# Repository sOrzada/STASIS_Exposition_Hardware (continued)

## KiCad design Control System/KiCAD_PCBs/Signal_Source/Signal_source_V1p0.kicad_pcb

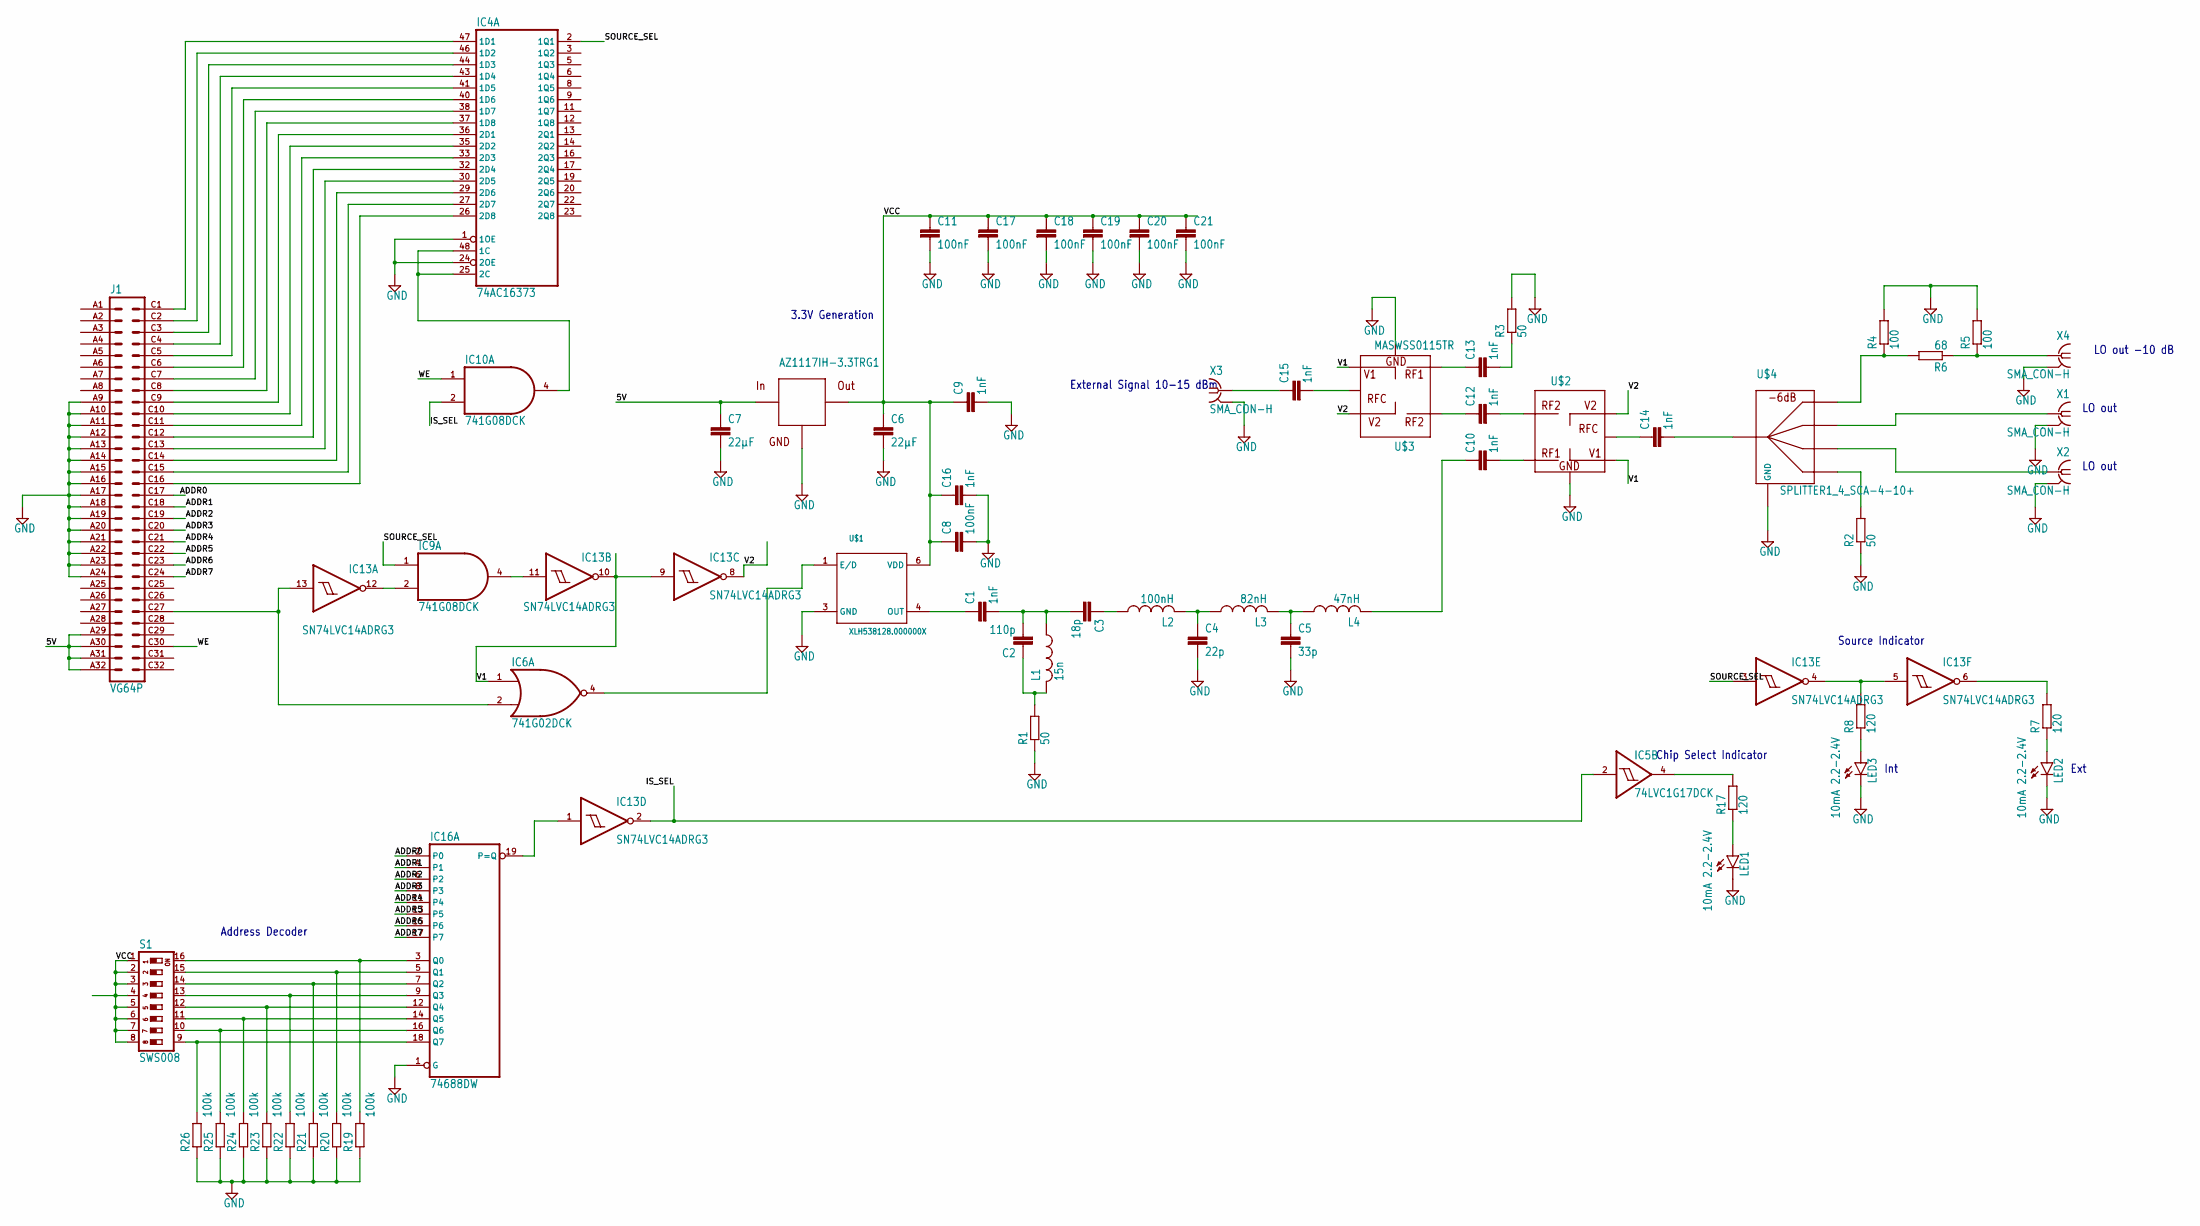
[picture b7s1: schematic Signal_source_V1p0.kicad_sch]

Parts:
C1, C9, C10, C12, C13, C14, C15, C16: 1nF; C0805
C2: 110p; C0805
C3: 18p; C0805
C4: 22p; C0805
C5: 33p; C0805
C6, C7: 22µF; C1206
C8, C11, C17, C18, C19, C20, C21: 100nF; C1206
IC4: 74AC16373; SSOP48DL
IC5: 74LVC1G17DCK; SC70-5
IC6: 741G02DCK; SC70-5
IC9, IC10: 741G08DCK; SC70-5
IC13: SN74LVC14ADRG3; SO14
IC16: 74688DW; SO20W
J1: VG64P
L1: 15n; L3225M
L2: 100nH; L3225M
L3: 82nH; L3225M
L4: 47nH; L3225M
LED1, LED2, LED3: 10mA 2.2-2.4V; LED3MM
R1, R2, R3: 50; R0805
R4, R5: 100; R0805
R6: 68; R0805
R7, R8, R17: 120; R0603
R19, R20, R21, R22, R23, R24, R25, R26: 100k; R0603
S1: SWS008; SMS-008
U$1: XLH538128.000000X; 5.0X3.2_XO
U$2, U$3: MASWSS0115TR; SC70-6
U$4: SPLITTER1_4_SCA-4-10+; SCA-4-10+
U$9: AZ1117IH-3.3TRG1; SOT223
X1, X2, X3, X4: SMA_CON-H; BU-SMA-H

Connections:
5V: C7.1, J1.A29, J1.A30, J1.A31, J1.A32, U$9.3 (IN)
ADDR0: IC16.2 (P0), J1.C17
ADDR1: IC16.4 (P1), J1.C18
ADDR2: IC16.6 (P2), J1.C19
ADDR3: IC16.8 (P3), J1.C20
ADDR4: IC16.11 (P4), J1.C21
ADDR5: IC16.13 (P5), J1.C22
ADDR6: IC16.15 (P6), J1.C23
ADDR7: IC16.17 (P7), J1.C24
CLK_128: C1.1, U$1.4 (OUT)
GND: C4.2, C5.2, C6.2, C7.2, C8.2, C9.2, C11.2, C16.2, C17.2, C18.2, C19.2, C20.2, C21.2, IC4.1 (1OE), IC4.4 (GND@1), IC4.10 (GND@2), IC4.15 (GND@3), IC4.21 (GND@4), IC4.24 (2OE), IC4.28 (GND@5), IC4.34 (GND@6), IC4.39 (GND@7), IC4.45 (GND@8), IC5.3 (GND), IC6.3 (GND), IC9.3 (GND), IC10.3 (GND), IC13.7 (GND), IC16.1 (G), IC16.10 (GND), J1.A9, J1.A10, J1.A11, J1.A12, J1.A13, J1.A14, J1.A15, J1.A16, J1.A17, J1.A18, J1.A19, J1.A20, J1.A21, J1.A22, J1.A23, J1.A24, LED1.K (C), LED2.K (C), LED3.K (C), R1.1, R2.1, R3.2, R4.2, R5.2, R19.1, R20.1, R21.1, R22.1, R23.1, R24.1, R25.1, R26.1, U$1.3 (GND), U$2.2 (GND), U$3.2 (GND), U$4.P$1 (GND), U$4.P$2 (GND), U$4.P$4 (GND), U$4.P$5 (GND), U$4.P$8 (GND), U$9.1 (GND), X1.2 (GND@1), X1.3 (GND@1), X1.4 (GND@1), X1.5 (GND@1), X2.2 (GND@1), X2.3 (GND@1), X2.4 (GND@1), X2.5 (GND@1), X3.2 (GND@1), X3.3 (GND@1), X3.4 (GND@1), X3.5 (GND@1), X4.2 (GND@1), X4.3 (GND@1), X4.4 (GND@1), X4.5 (GND@1)
IS_SEL: IC5.2 (I), IC10.2 (I1), IC13.2 (O)
unnamed: IC4.47 (1D1), J1.C1
unnamed: C1.2, C2.2, C3.2, L1.1
unnamed: C2.1, L1.2, R1.2
unnamed: C3.1, L2.1
unnamed: C4.1, L2.2, L3.1
unnamed: C5.1, L3.2, L4.1
unnamed: IC4.46 (1D2), J1.C2
unnamed: IC4.44 (1D3), J1.C3
unnamed: C10.1, L4.2
unnamed: IC4.43 (1D4), J1.C4
unnamed: IC4.41 (1D5), J1.C5
unnamed: IC4.40 (1D6), J1.C6
unnamed: C10.2, U$2.1 (RF1)
unnamed: IC4.38 (1D7), J1.C7
unnamed: IC4.37 (1D8), J1.C8
unnamed: C12.1, U$3.3 (RF2)
unnamed: C12.2, U$2.3 (RF2)
unnamed: C13.1, U$3.1 (RF1)
unnamed: C13.2, R3.1
unnamed: C15.2, U$3.5 (RFC)
unnamed: C14.1, U$2.5 (RFC)
unnamed: C14.2, U$4.P$3
unnamed: C15.1, X3.1
unnamed: IC9.2 (I1), IC13.12 (O)
unnamed: IC4.36 (2D1), J1.C9
unnamed: IC4.35 (2D2), J1.C10
unnamed: IC4.33 (2D3), J1.C11
unnamed: IC4.32 (2D4), J1.C12
unnamed: IC4.30 (2D5), J1.C13
unnamed: IC4.29 (2D6), J1.C14
unnamed: IC4.27 (2D7), J1.C15
unnamed: IC4.26 (2D8), J1.C16
unnamed: IC6.4 (O), U$1.1 (E/D)
unnamed: IC6.2 (I1), IC13.13 (I), J1.C27
unnamed: IC9.4 (O), IC13.11 (I)
unnamed: IC4.25 (2C), IC4.48 (1C), IC10.4 (O)
unnamed: U$4.P$7, X1.1
unnamed: U$4.P$9, X2.1
unnamed: R2.2, U$4.P$10
unnamed: IC16.3 (Q0), R19.2, S1.16
unnamed: R4.1, R6.2, U$4.P$6
unnamed: R5.1, R6.1, X4.1
unnamed: IC13.4 (O), IC13.5 (I), R8.2
unnamed: IC13.6 (O), R7.2
unnamed: LED3.A, R8.1
unnamed: LED2.A, R7.1
unnamed: IC16.5 (Q1), R20.2, S1.15
unnamed: IC16.7 (Q2), R21.2, S1.14
unnamed: IC16.9 (Q3), R22.2, S1.13
unnamed: IC16.12 (Q4), R23.2, S1.12
unnamed: IC16.14 (Q5), R24.2, S1.11
unnamed: IC16.16 (Q6), R25.2, S1.10
unnamed: IC16.18 (Q7), R26.2, S1.9
unnamed: IC13.1 (I), IC16.19 (P=Q)
unnamed: LED1.A, R17.1
unnamed: IC5.4 (O), R17.2
SOURCE_SEL: IC4.2 (1Q1), IC9.1 (I0), IC13.3 (I)
V1: IC6.1 (I0), IC13.9 (I), IC13.10 (O), U$2.6 (V1), U$3.6 (V1)
V2: IC13.8 (O), U$2.4 (V2), U$3.4 (V2)
VCC: C6.1, C8.1, C9.1, C11.1, C16.1, C17.1, C18.1, C19.1, C20.1, C21.1, IC4.7 (VCC@1), IC4.18 (VCC@2), IC4.31 (VCC@3), IC4.42 (VCC@4), IC5.5 (VCC), IC6.5 (VCC), IC9.5 (VCC), IC10.5 (VCC), IC13.14 (VCC), IC16.20 (VCC), S1.1, S1.2, S1.3, S1.4, S1.5, S1.6, S1.7, S1.8, U$1.6 (VDD), U$9.2 (OUT), U$9.4 (OUT)
WE: IC10.1 (I0), J1.C30

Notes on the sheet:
3.3V Generation
LO out
Ext
Address Decoder
Chip Select Indicator
Int
External Signal 10-15 dBm
LO out -10 dB
Source Indicator

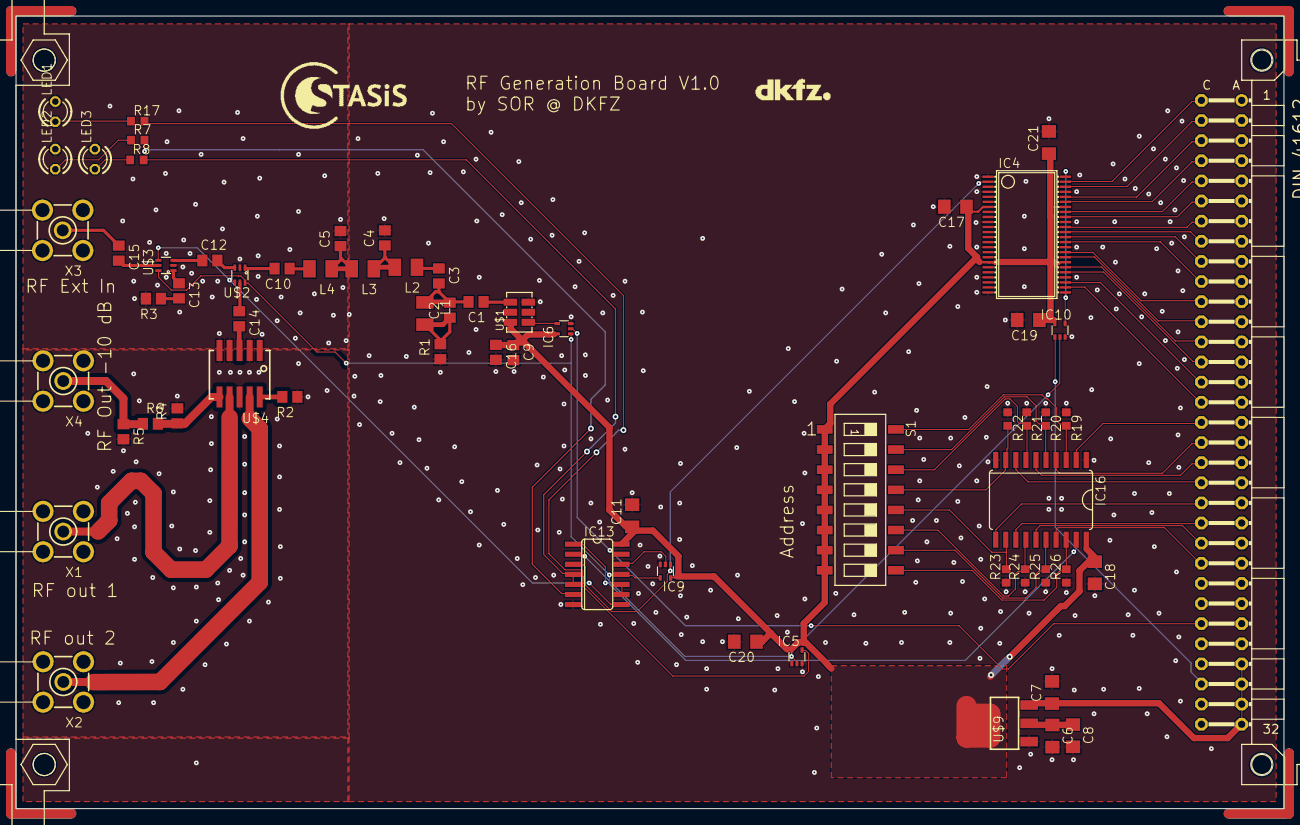
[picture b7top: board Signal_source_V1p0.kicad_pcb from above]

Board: 2 copper layers, 160.0 x 100.0 mm, 65 parts (0 on the bottom side), 73 nets.

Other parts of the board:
U$5: LOGO_STASIS
U$6: LOGO_DKFZ

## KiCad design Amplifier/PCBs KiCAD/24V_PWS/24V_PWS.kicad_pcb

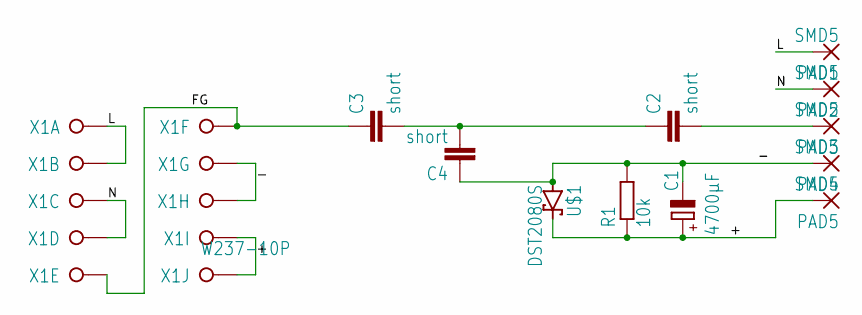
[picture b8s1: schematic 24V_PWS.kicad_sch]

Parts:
C1: 4700µF; E7,5-18
C2, C3, C4: short; C1206
PAD1, PAD2, PAD3, PAD4, PAD5: SMD5; SMD2,54-5,08
R1: 10k; R2012
U$1: DST2080S; TO-277B
X1: W237-10P

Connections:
+: C1.+, PAD5.1, R1.1, U$1.P$1 (C), X1.9, X1.10
-: C1.-, C4.1, PAD4.1, R1.2, U$1.P$2 (A), U$1.P$3 (A), X1.7, X1.8
FG: C3.1, X1.5, X1.6
L: PAD1.1, X1.1, X1.2
N: PAD2.1, X1.3, X1.4
unnamed: C2.2, PAD3.1
unnamed: C2.1, C3.2, C4.2

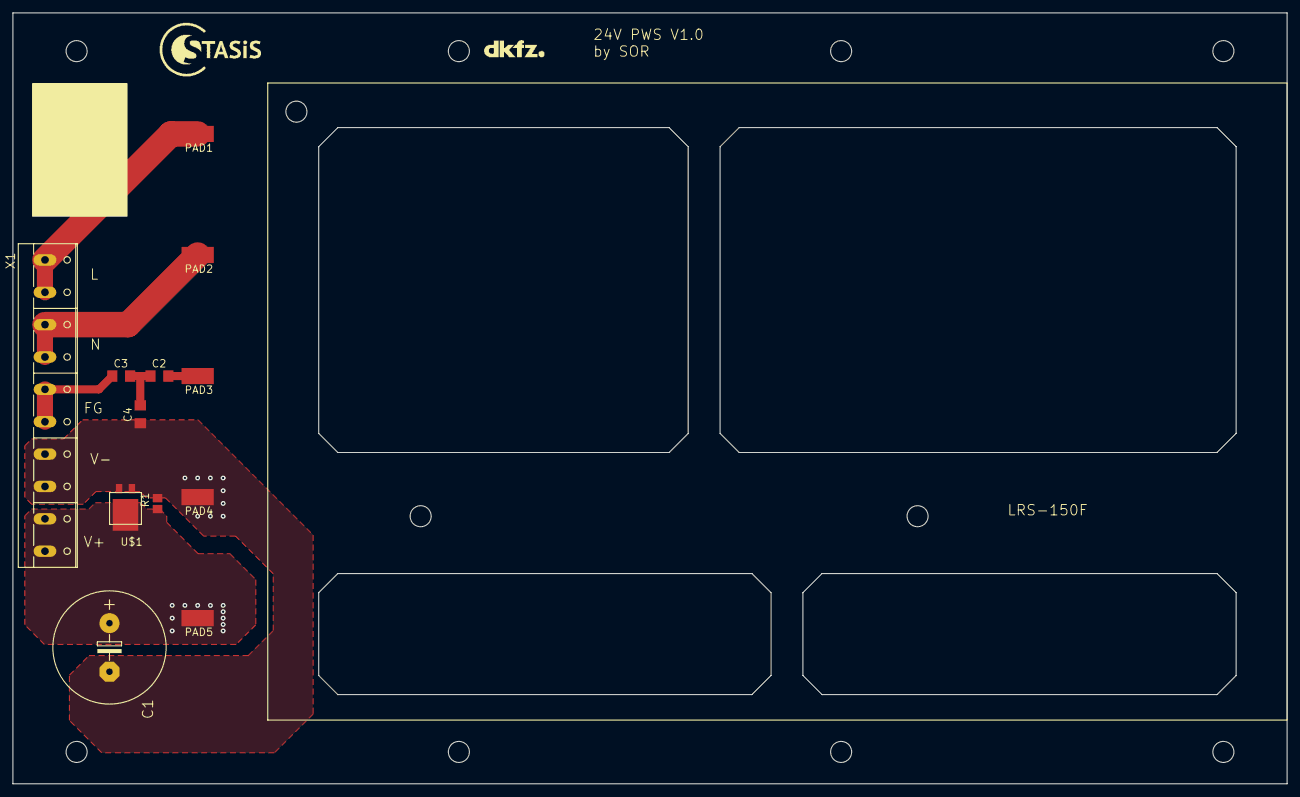
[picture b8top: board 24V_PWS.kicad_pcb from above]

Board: 2 copper layers, 200.0 x 121.0 mm, 25 parts (0 on the bottom side), 7 nets.

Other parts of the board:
@HOLE0, @HOLE1, @HOLE2, @HOLE3, @HOLE4, @HOLE5, @HOLE6, @HOLE7, @HOLE8, @HOLE9, @HOLE10: (no value)
U$2: LOGO_STASIS
U$3: LOGO_DKFZ

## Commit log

2025-02-12 Upload Array data and Main Documentation Document.
2025-02-12 Upload PCBs and Housing
2025-02-12 Deleted Backup of Documentation Document.
2025-02-12 Added Name to Readme
2025-02-12 Changed Readme
2025-02-12 Added Spice Simulations
    -HPA
    -2nd stage amplifier
    -Voltage Control
2025-02-12 Create LICENSE
    Added License
2025-02-12 Create Disclaimer.txt
    Created disclaimer.
2025-02-12 Closed KiCad, which changed a backup file.
2025-02-17 Expanded Documentation Included warnings Included description of GUI (not finished yet).
2025-03-19 Updated Calibration Changed the way the calibration should be done and changed the documentation accordingly.
2025-09-16 Added Fusion360 file for array housing
2025-09-16 Added Partlist
    Added partlist with prices at time of purchase.
2025-09-30 Added more explanation to readme
